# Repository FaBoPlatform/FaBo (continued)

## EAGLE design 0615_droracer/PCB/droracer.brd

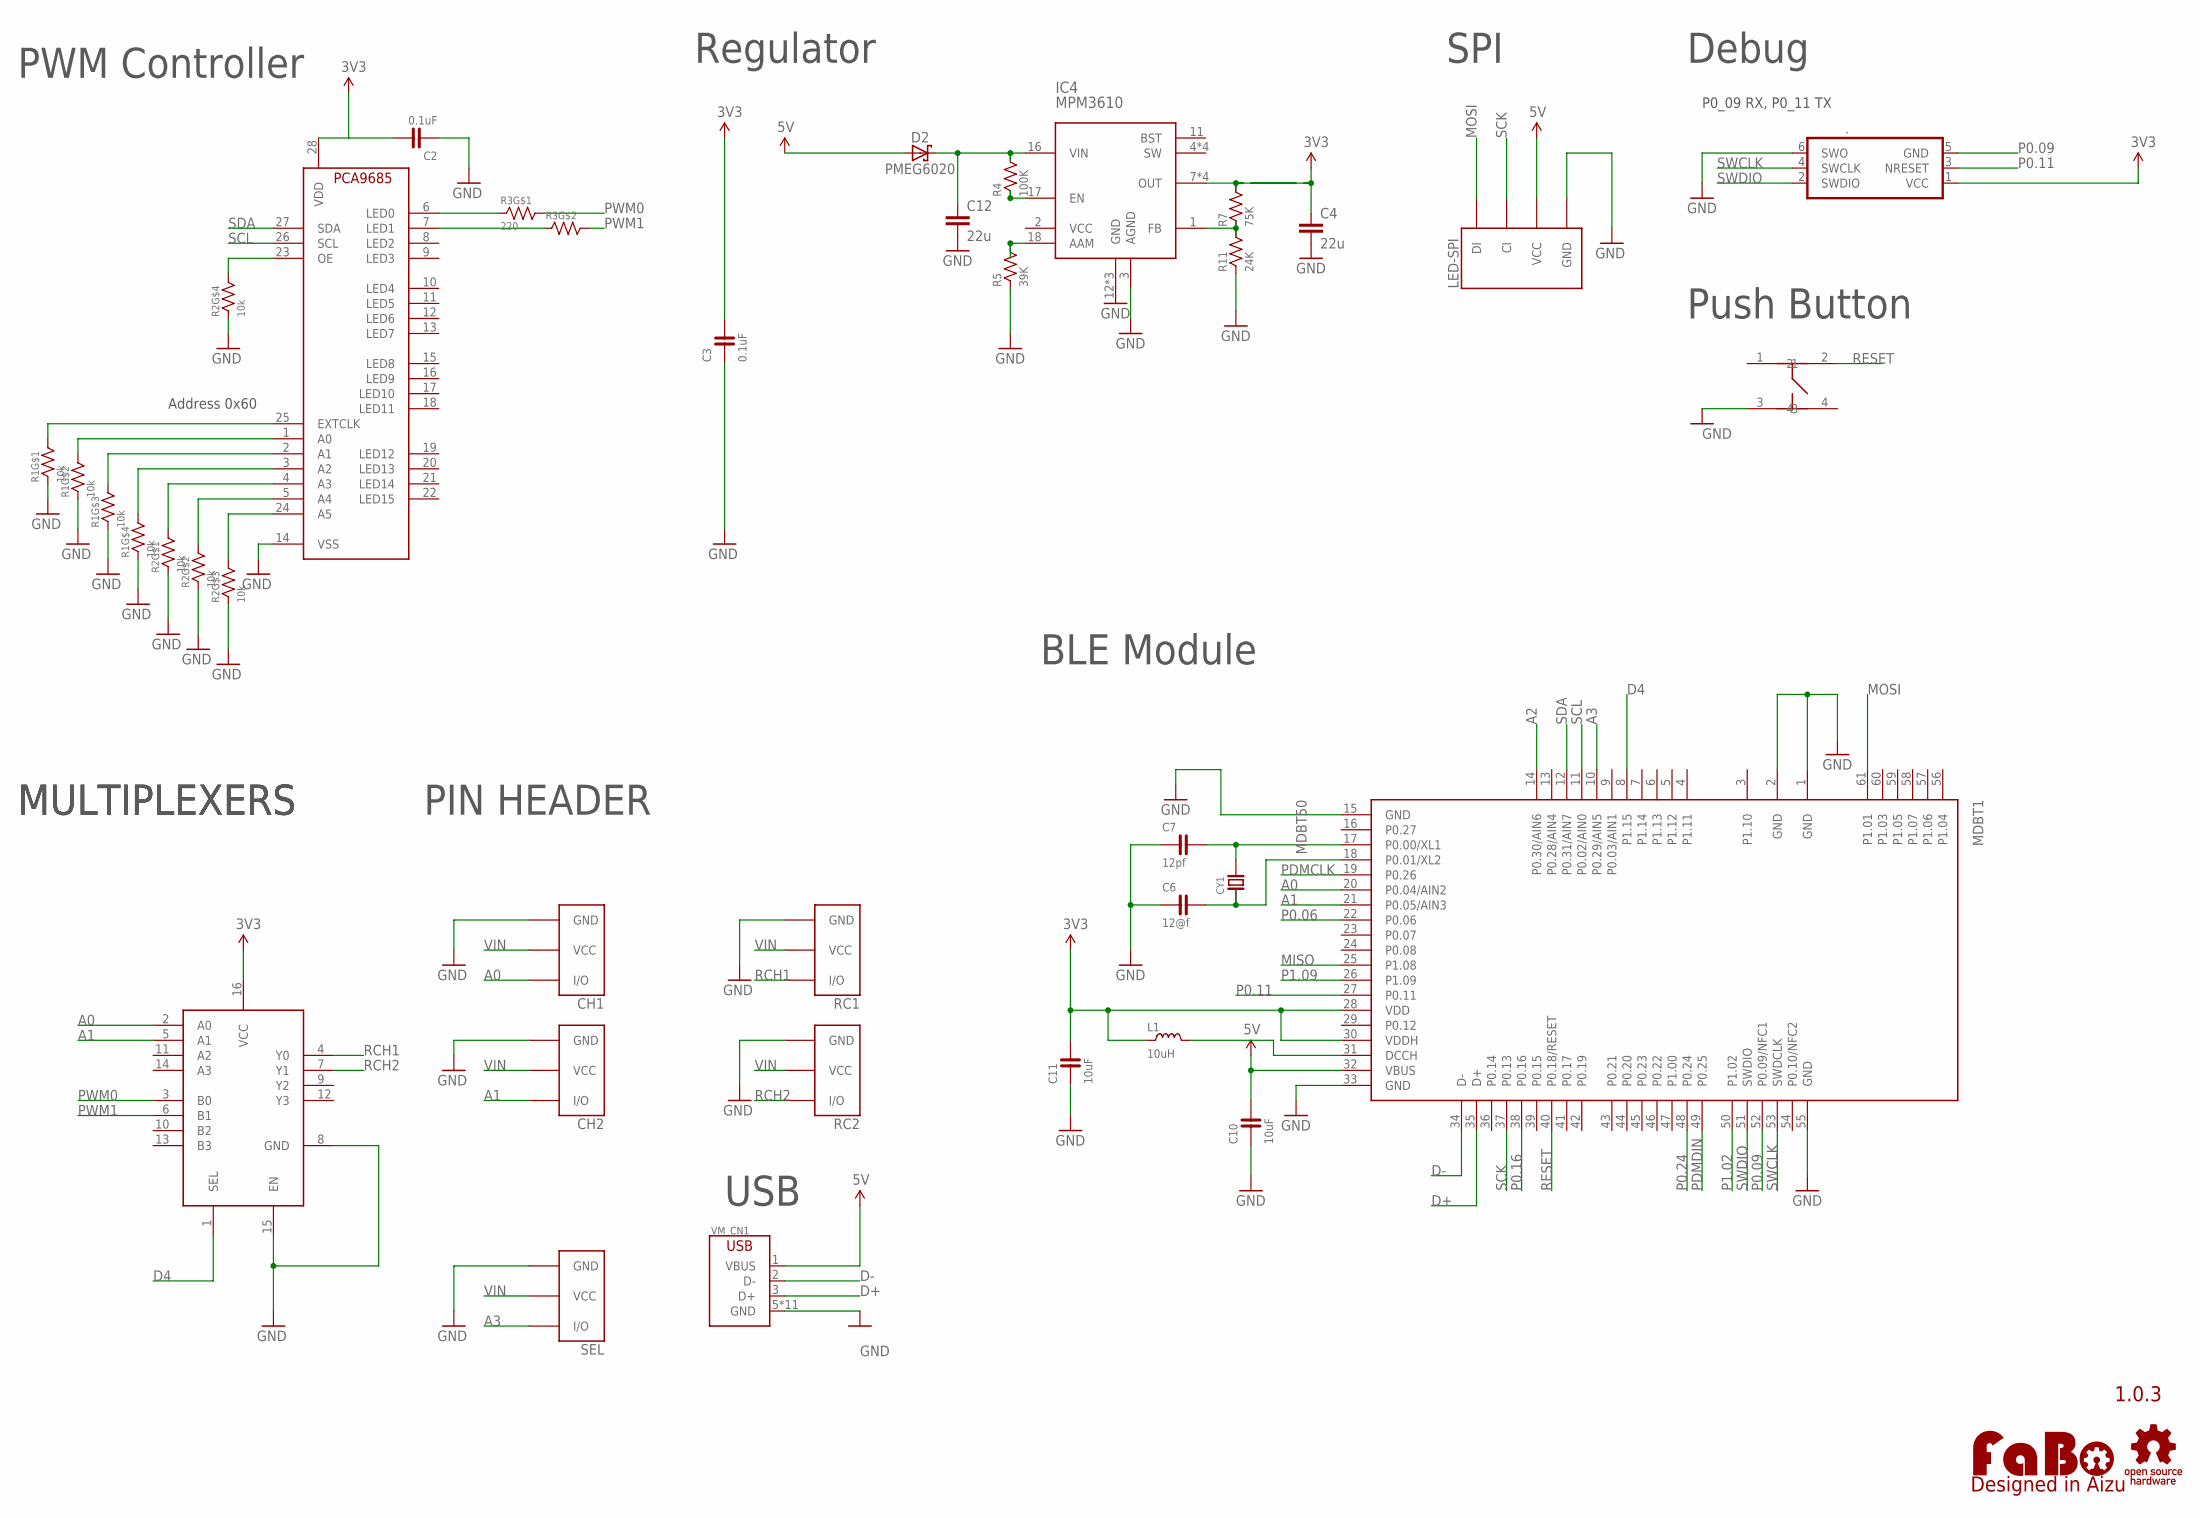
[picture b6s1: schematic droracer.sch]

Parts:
.: TC2030-IDC-NL
C2, C3: 0.1uF; 0603
C4, C12: 22u; 0805-R2013X50N
C6: 12@f; 0603
C7: 12pf; 0603
C10, C11: 10uF; 0603
CH1, CH2: FABO_BRICK_3PIN-HEADER; FABO_BRICK_3PIN_HEADER
CY1: CRYSTAL-ABS07; ABRACON-ABS07-32.768KHZ
D2: PMEG6020; SODFL3517X110N
IC3: MULTIPLEXERSMC74HC157A; TSSOP-16
IC4: MPM3610
L1: 10uH; 0603
LED-SPI: FABO-SPI-LED-B04B; SPI-B04B-PASK-1
MDBT1: MDBT50
R1, R2: 10k; EXBV8V
R3: 220; EXBV8V
R4: 100K; 0603
R5: 39K; 0603
R7: 75K; 0603
R11: 24K; 0603
RC1, RC2: FABO_BRICK_3PIN-HEADER; FABO_BRICK_3PIN_HEADER
SEL: FABO_BRICK_3PIN-HEADER; FABO_BRICK_3PIN_HEADER
U$2: PCA9685
U$3: LOGO_OSHW-M_BOTTOM; LOGO_OSHW_M_BOTTOM
U$4: LOGO_FABO-M; LOGO_FABO_MS
U$5: SWICTH-4P(KMR2); SWITCH-4P(KMR2)
VM_CN1: USB-ZX62D; ZX62D-B-5PA8

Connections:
3V3: ..1 (VCC), C2.2, C3.2, C4.1, C11.2, IC3.16 (VCC), IC4.7 (OUT), IC4.8 (OUT), IC4.9 (OUT), IC4.20 (OUT), L1.1, MDBT1.28 (VDD), MDBT1.30 (VDDH), R7.2, U$2.28 (VDD)
5V: C10.2, D2.A, LED-SPI.VCC, MDBT1.32 (VBUS), VM_CN1.1 (VBUS)
A0: CH1.I/O, IC3.2 (A0), MDBT1.20 (P0.04/AIN2)
A1: CH2.I/O, IC3.5 (A1), MDBT1.21 (P0.05/AIN3)
A2: MDBT1.14 (P0.30/AIN6)
A3: MDBT1.10 (P0.29/AIN5), SEL.I/O
D4: IC3.1 (SEL), MDBT1.8 (P1.15)
D+: MDBT1.35 (D+), VM_CN1.3 (D+)
D-: MDBT1.34 (D-), VM_CN1.2 (D-)
FB: IC4.1 (FB), R7.1, R11.2
GND: ..6 (SWO), C2.1, C3.1, C4.2, C6.1, C7.1, C10.1, C11.1, C12.2, CH1.GND, CH2.GND, IC3.8 (GND), IC3.15 (EN), IC4.3 (AGND), IC4.12 (GND), IC4.13 (GND), IC4.14 (GND), LED-SPI.GND, MDBT1.1 (GND), MDBT1.2 (GND), MDBT1.15 (GND), MDBT1.33 (GND), MDBT1.55 (GND), R1.1, R1.2 (1), R1.3 (1), R1.4 (1), R2.1, R2.2 (1), R2.3 (1), R2.4 (1), R5.1, R11.1, RC1.GND, RC2.GND, SEL.GND, U$2.14 (VSS), U$5.3, VM_CN1.5 (GND), VM_CN1.B1 (GND), VM_CN1.B2 (GND), VM_CN1.B3 (GND), VM_CN1.B4 (GND), VM_CN1.T1 (GND), VM_CN1.T2 (GND), VM_CN1.T3 (GND), VM_CN1.T4 (GND), VM_CN1.T5 (GND), VM_CN1.T6 (GND)
MISO: MDBT1.25 (P1.08)
MOSI: LED-SPI.DI, MDBT1.61 (P1.01)
unnamed: R3.1, U$2.6 (LED0)
unnamed: R3.2 (1), U$2.7 (LED1)
unnamed: IC4.17 (EN), R4.1
unnamed: C12.1, D2.C, IC4.16 (VIN), R4.2
unnamed: IC4.18 (AAM), R5.2
unnamed: R2.5 (2), U$2.23 (OE)
unnamed: R1.8 (2), U$2.25 (EXTCLK)
unnamed: R1.7 (2), U$2.1 (A0)
unnamed: R1.6 (2), U$2.2 (A1)
unnamed: R1.5 (2), U$2.3 (A2)
unnamed: R2.8 (2), U$2.4 (A3)
unnamed: R2.7 (2), U$2.5 (A4)
unnamed: R2.6 (2), U$2.24 (A5)
unnamed: C7.2, CY1.P$2, MDBT1.17 (P0.00/XL1)
unnamed: C6.2, CY1.P$1, MDBT1.18 (P0.01/XL2)
unnamed: L1.2, MDBT1.31 (DCCH)
P0.06: MDBT1.22 (P0.06)
P0.09: ..5 (GND), MDBT1.52 (P0.09/NFC1)
P0.11: ..3 (NRESET), MDBT1.27 (P0.11)
P0.16: MDBT1.38 (P0.16)
P0.24: MDBT1.48 (P0.24)
P1.02: MDBT1.50 (P1.02)
P1.09: MDBT1.26 (P1.09)
PDMCLK: MDBT1.19 (P0.26)
PDMDIN: MDBT1.49 (P0.25)
PWM0: IC3.3 (B0), R3.8 (2)
PWM1: IC3.6 (B1), R3.7 (2)
RCH1: IC3.4 (Y0), RC1.I/O
RCH2: IC3.7 (Y1), RC2.I/O
RESET: MDBT1.40 (P0.18/RESET), U$5.2
SCK: LED-SPI.CI, MDBT1.37 (P0.13)
SCL: MDBT1.11 (P0.02/AIN0), U$2.26 (SCL)
SDA: MDBT1.12 (P0.31/AIN7), U$2.27 (SDA)
SWCLK: ..4 (SWCLK), MDBT1.53 (SWDCLK)
SWDIO: ..2 (SWDIO), MDBT1.51 (SWDIO)
VIN: CH1.VCC, CH2.VCC, RC1.VCC, RC2.VCC, SEL.VCC

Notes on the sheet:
1.0.3
PWM Controller
MULTIPLEXERS
Address 0x60
PIN HEADER
Regulator
SPI
USB
Push Button
BLE Module
Debug
P0_09 RX, P0_11 TX

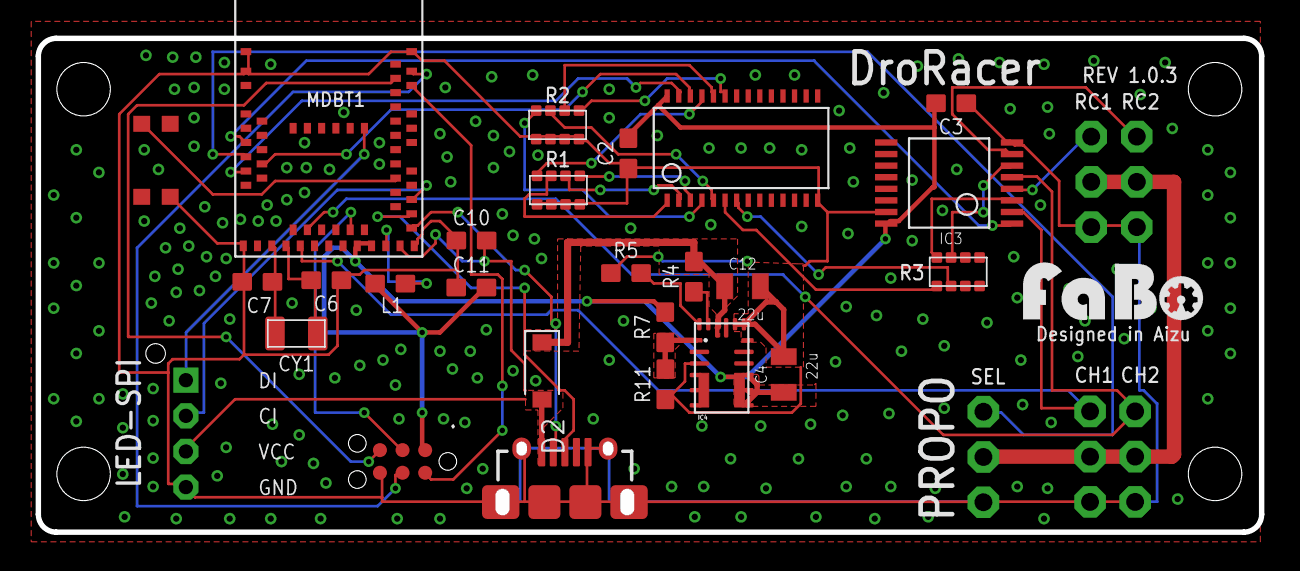
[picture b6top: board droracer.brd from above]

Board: 2 copper layers, 68.7 x 27.7 mm, 33 parts (0 on the bottom side), 40 nets.
